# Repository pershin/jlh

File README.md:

# JLH
Усилитель JLH на отечественных транзисторах (КТ361Г, КТ801А и 2Т803А)

## Технические параметры
Количество каналов: 2\
Напряжение питания: 12... 17В\
Сопротивление нагрузки: 4 Ω

## Электронные компоненты

### Транзисторы биполярные
Наименование | Кол-во
--- | :---:
КТ361Г | 2
КТ801А | 2
2Т803А | 4

### Конденсаторы
Наименование | Кол-во
--- | :---:
0,1 мкФ 250 В | 2
KZK White Line 2,2 мкФ 250 В 5% | 2
Epcos 100 мкФ 50 В | 2
Nichicon KZ 50V 220 uF | 2
Epcos 470 мкФ 25 В | 2
2200 мкФ 50 В | 2
Nichicon FW 35V 4700 uF | 2

### Резисторы
Наименование | Кол-во
--- | :---:
47 Ω 0,5 Вт | 2
Р1-7 180 Ω 2 Вт ±10% | 2
ОМЛТ-0,5 220 Ω ±5% | 2
ОМЛТ-0,5 2,2 кОм ±5% | 2
ОМЛТ-0,5 2,7 кОм ±5% | 2
МЛТ-0,5 8,2 кОм ±5% | 2
ОМЛТ-0,5 39 кОм ±5% | 2
МЛТ-0,5 100 кОм ±5% | 4

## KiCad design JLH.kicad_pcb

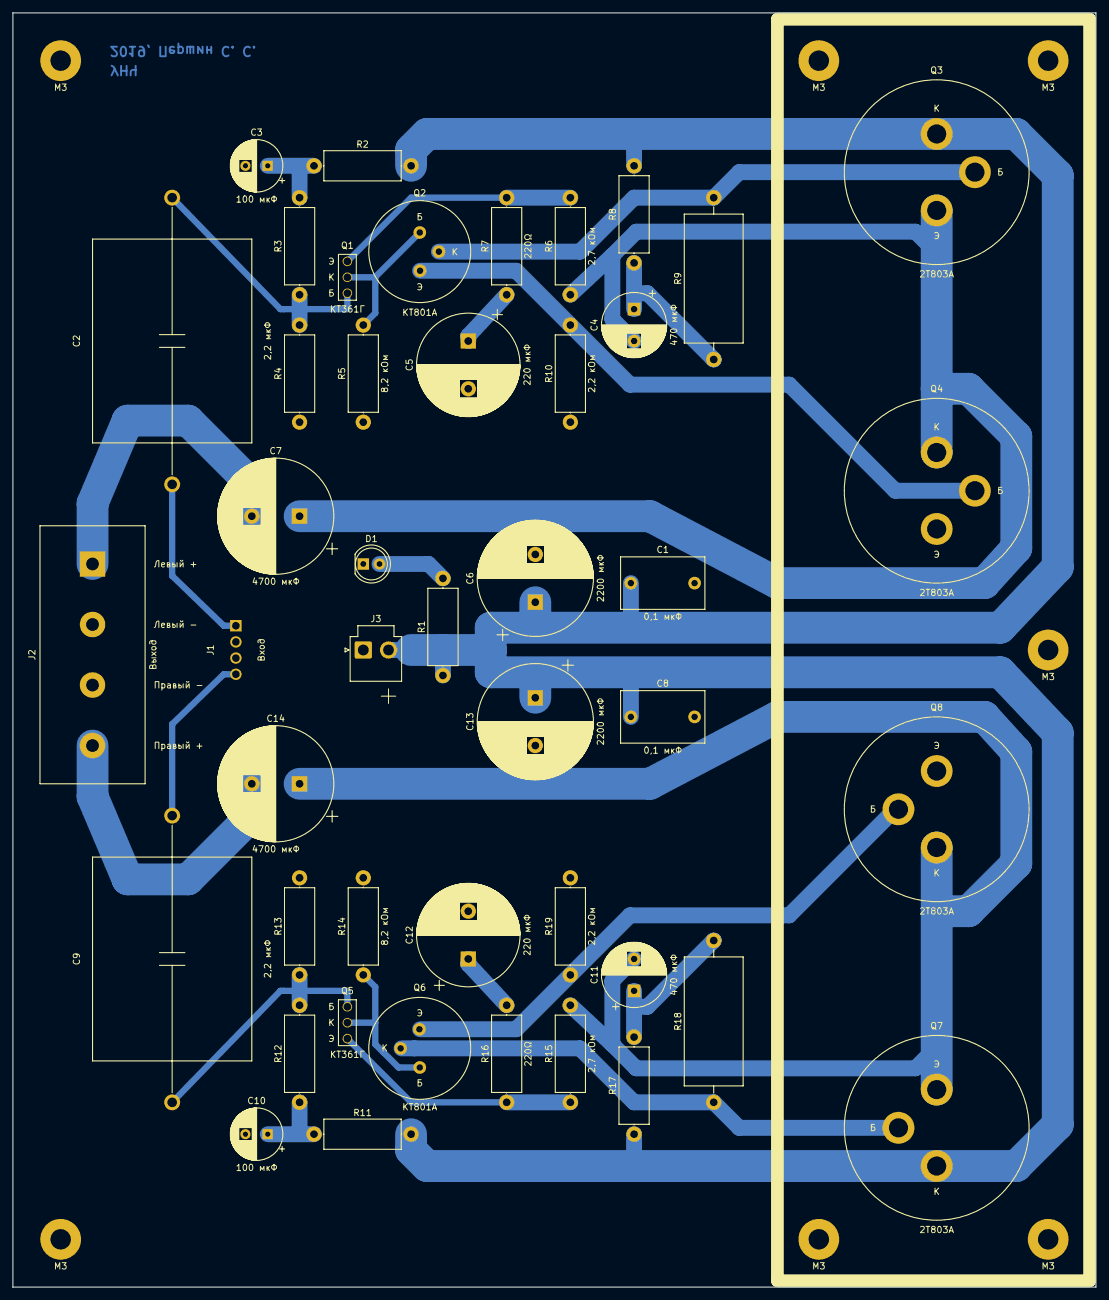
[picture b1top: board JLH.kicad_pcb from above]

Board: 2 copper layers, 170.0 x 200.0 mm, 52 parts (0 on the bottom side), 25 nets.

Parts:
C1, C8: 0,1 мкФ; C_Rect_L13.0mm_W8.0mm_P10.00mm_FKS3_FKP3_MKS4
C2, C9: 2,2 мкФ; KZK_White_Line_L32.0mm_D25.0mm_P45.00mm_Horizontal
C3, C10: 100 мкФ; CP_Radial_D8.0mm_P3.50mm
C4, C11: 470 мкФ; CP_Radial_D10.0mm_P5.00mm
C5, C12: 220 мкФ; CP_Radial_D16.0mm_P7.50mm
C6, C13: 2200 мкФ; CP_Radial_D18.0mm_P7.50mm
C7, C14: 4700 мкФ; CP_Radial_D18.0mm_P7.50mm
D1: LED; LED_D5.0mm
H1, H2, H3, H4, H5, H6, H7: M3; MountingHole_3.2mm_M3_Pad
J1: Вход; 5-103639-3
J2: Выход; T34-BM11-04
J3: B2P-VH; JST_VH_B2P-VH_1x02_P3.96mm_Vertical
Q1, Q5: КТ361Г; kt-13
Q2, Q6: КТ801А; kt801
Q3, Q4, Q7, Q8: 2Т803А; 2t803a
R1, R10, R19: 2,2 кОм; R_Axial_DIN0414_L11.9mm_D4.5mm_P15.24mm_Horizontal
R2, R11: 39 кОм; R_Axial_DIN0414_L11.9mm_D4.5mm_P15.24mm_Horizontal
R3, R4, R12, R13: 100 кОм; R_Axial_DIN0414_L11.9mm_D4.5mm_P15.24mm_Horizontal
R5, R14: 8,2 кОм; R_Axial_DIN0414_L11.9mm_D4.5mm_P15.24mm_Horizontal
R6, R15: 2,7 кОм; R_Axial_DIN0414_L11.9mm_D4.5mm_P15.24mm_Horizontal
R7, R16: 220Ω; R_Axial_DIN0414_L11.9mm_D4.5mm_P15.24mm_Horizontal
R8, R17: 47Ω; R_Axial_DIN0414_L11.9mm_D4.5mm_P15.24mm_Horizontal
R9, R18: 180Ω; R_Axial_DIN0922_L20.0mm_D9.0mm_P25.40mm_Horizontal

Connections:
/Левый канал/IN+: C2.1, J1.1
/Левый канал/OUT+: C7.2, J2.1
/Левый канал/VCC: C1.1, C6.1, C8.1, C13.1, J3.2, Q3.1, Q7.1, R1.1, R2.1, R8.1, R11.1, R17.1
/Правый канал/IN+: C9.1, J1.4
/Правый канал/OUT+: C14.2, J2.4
GND: C1.2, C3.2, C5.2, C6.2, C8.2, C10.2, C12.2, C13.2, D1.1, J1.2, J1.3, J2.2, J2.3, J3.1, Q4.3, Q8.3, R4.2, R5.2, R10.2, R13.2, R14.2, R19.2
unnamed: C2.2, Q1.3, R3.2, R4.1
unnamed: C3.1, R2.2, R3.1
unnamed: C4.1, R8.2, R9.2
unnamed: C4.2, C7.1, Q3.3, Q4.1, R6.2
unnamed: C5.1, R7.2
unnamed: C9.2, Q5.3, R12.2, R13.1
unnamed: C10.1, R11.2, R12.1
unnamed: C11.1, R17.2, R18.2
unnamed: C11.2, C14.1, Q7.3, Q8.1, R15.2
unnamed: C12.1, R16.2
unnamed: D1.2, R1.2
unnamed: Q1.1, R6.1, R7.1
unnamed: Q1.2, Q2.1, R5.1
unnamed: Q2.2, Q3.2, R9.1
unnamed: Q2.3, Q4.2, R10.1
unnamed: Q5.1, R15.1, R16.1
unnamed: Q5.2, Q6.1, R14.1
unnamed: Q6.2, Q7.2, R18.1
unnamed: Q6.3, Q8.2, R19.1

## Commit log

2019-05-16 Updated paths to 3d models
2019-05-16 Removed potentiometer
2019-05-19 Added 2T803A
2019-05-19 Update 2T803A
2019-05-19 Added 3d model for 2T803A
2019-05-19 Updated 3d model for 2T803A
2019-05-19 Updated 3d model for KT801
2019-06-07 Assigned footprints for capacitors
2019-06-07 Assigned footprint for power connector
2019-06-08 Updated resistors
2019-06-10 Updated PCB (one channel)
2019-06-15 Added I/O terminals
2019-06-15 Added scheme for 2 channel (stereo)
2019-06-21 Added hierarchical sheet for L/R channels
2019-06-21 New annotation
2019-07-06 Updated PCB
2019-07-15 Added filled zones
2019-07-17 Added mounting holes
2019-08-29 Added capacitors
2019-10-21 Fixed polarity
2019-10-22 Removed top layer
2019-10-22 Added author to PCB
2019-10-23 Updated output directory
2019-10-24 Fixed GND
2019-10-24 Added mounting hole
2019-10-25 Created gerber and drill files
